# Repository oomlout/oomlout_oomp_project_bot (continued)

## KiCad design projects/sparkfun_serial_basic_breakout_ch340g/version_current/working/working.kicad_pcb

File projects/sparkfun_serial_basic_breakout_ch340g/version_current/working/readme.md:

# Serial_Basic_Breakout-CH340G by sparkfun  
This is a harvested standardized copy of a project from github.  
The original project can be found at:  
https://github.com/sparkfun/Serial_Basic_Breakout-CH340G  
Please consult that link for additional, details, files, and license information.  
Note: It was auto harvested and if the original repo had more than one board file or anything out of the ordinary the files here are likely not representative.

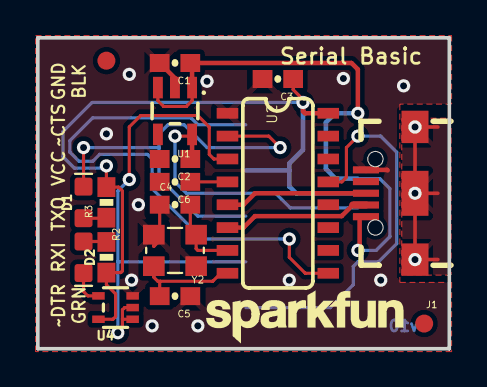
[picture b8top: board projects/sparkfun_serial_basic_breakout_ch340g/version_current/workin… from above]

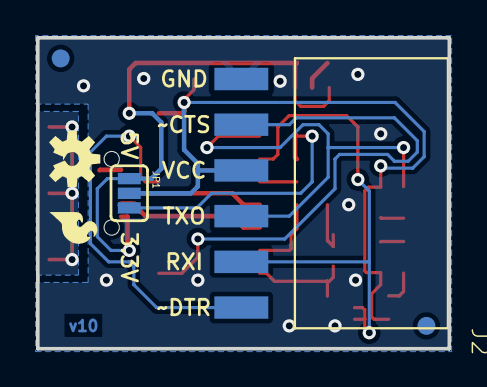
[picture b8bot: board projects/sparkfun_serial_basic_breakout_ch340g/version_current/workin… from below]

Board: 2 copper layers, 22.9 x 17.3 mm, 25 parts (6 on the bottom side), 17 nets.

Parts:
C1, C2: 1.0uF; 0603-CAP
C3: 0.1uF; 0603-CAP
C4, C5: 10pF; 0603-CAP
C6: 10nF; 0603-CAP
D1: GREEN; LED-0603
D2: Yellow; LED-0603
FRAME1: FRAME-LETTER; CREATIVE_COMMONS
J1: microB; USB-B-MICRO-SMD_V03
J2: 1X06-SMD-FEMALE-V2
JP1: PAD-JUMPER-3-2OF3_NC_BY_PASTE_YES_SILK_FULL_BOX
JP3, JP4, JP5, JP6: FIDUCIAL1X2; FIDUCIAL-1X2
LOGO1: OSHW-LOGOS; OSHW-LOGO-S
LOGO2: SFE_LOGO_FLAME.1_INCH; SFE_LOGO_FLAME_.1
LOGO3: SFE_LOGO_NAME.1_INCH; SFE_LOGO_NAME_.1
R2: 1K; 0603-RES
R3: 330; 0603-RES
U1: AP2112-3.3V; SOT23-5
U2: CH340G; SO016
U4: 74LVC1G08SE; SOT353
Y2: 12MHz; CRYSTAL-SMD-3.2X2.5

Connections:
3.3V: C2.1, JP1.3, U1.5
5V: C1.1, J1.VBUS, JP1.1, U1.1, U1.3
GND: C1.2, C2.2, C3.2, C4.1, C5.1, C6.2, J1.GND, J2.1, U1.2, U2.1, U4.3, Y2.2, Y2.4
unnamed: D1.A, R3.1
unnamed: D2.A, R2.1
unnamed: C5.2, U2.8, Y2.3
unnamed: C4.2, U2.7, Y2.1
unnamed: D2.C, U4.4
unnamed: J1.D-, U2.6
unnamed: J1.D+, U2.5
RXI: J2.5, U2.3, U4.1, U4.2
SHLD: J1.SHIELD1, J1.SHIELD2, J1.SHIELD3
TXO: D1.C, J2.4, U2.2
V3: C6.1, U2.4
VCC: C3.1, J2.3, JP1.2, R2.2, R3.2, U2.16, U4.5
~CTS: J2.2, U2.9
~DTR: J2.6, U2.13

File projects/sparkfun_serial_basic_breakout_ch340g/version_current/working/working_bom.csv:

"Id";"Designator";"Footprint";"Quantity";"Designation";"Supplier and ref";
1;"R3";"0603-RES";1;"330";;;
2;"JP4,JP3,JP5,JP6";"FIDUCIAL-1X2";4;"FIDUCIAL1X2";;;
3;"C1,C2";"0603-CAP";2;"1.0uF";;;
4;"C4,C5";"0603-CAP";2;"10pF";;;
5;"D2";"LED-0603";1;"Yellow";;;
6;"C6";"0603-CAP";1;"10nF";;;
7;"R2";"0603-RES";1;"1K";;;
8;"J1";"USB-B-MICRO-SMD_V03";1;"microB";;;
9;"U4";"SOT353";1;"74LVC1G08SE";;;
10;"FRAME1";"CREATIVE_COMMONS";1;"FRAME-LETTER";;;
11;"U1";"SOT23-5";1;"AP2112-3.3V";;;
12;"LOGO3";"SFE_LOGO_NAME_.1";1;"SFE_LOGO_NAME.1_INCH";;;
13;"Y2";"CRYSTAL-SMD-3.2X2.5";1;"12MHz";;;
14;"U2";"SO016";1;"CH340G";;;
15;"D1";"LED-0603";1;"GREEN";;;
16;"C3";"0603-CAP";1;"0.1uF";;;
17;"LOGO1";"OSHW-LOGO-S";1;"OSHW-LOGOS";;;
18;"J2";"1X06-SMD-FEMALE-V2";1;"";;;
19;"LOGO2";"SFE_LOGO_FLAME_.1";1;"SFE_LOGO_FLAME.1_INCH";;;
20;"JP1";"PAD-JUMPER-3-2OF3_NC_BY_PASTE_YES_SILK_FULL_BOX";1;"";;;

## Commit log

2023-07-30 a few generations
2023-07-31 some generations
2023-08-01 converted omerk brd to kicad
2023-08-02 a few projects
2023-08-02 some documentation
2023-08-03 more kicad files
2023-08-03 added kibot files for projects
2023-08-03 removed oom_kicad dependancy
2023-08-03 added print statement
2023-08-03 added kicad_sch check to deal with old kicad format issues
2023-08-03 more verbose command line arg.
2023-08-03 even more verbose.
2023-08-03 added an overwrite check
2023-08-03 first gitbot try
2023-08-03 up to date
2023-08-03 added some gitbot
2023-08-03 comitting after 1 generations
2023-08-03 comitting after 2 generations
2023-08-03 comitting after 30 generations
2023-08-03 comitting after 60 generations
2023-08-03 comitting after 90 generations
2023-08-03 comitting after 120 generations
2023-08-03 comitting after 150 generations
2023-08-03 comitting after 180 generations
2023-08-03 comitting after 210 generations
2023-08-03 comitting after 240 generations
2023-08-03 comitting after 270 generations
2023-08-03 comitting after 50 generations
2023-08-03 comitting after 100 generations
2023-08-03 comitting after 200 generations
2023-08-04 comitting after 250 generations
2023-08-04 comitting after 300 generations
2023-08-04 comitting after 350 generations
2023-08-04 comitting after 400 generations
2023-08-04 comitting after 450 generations
2023-08-04 comitting after 500 generations
2023-08-04 comitting after 550 generations
2023-08-04 comitting after 600 generations
2023-08-04 comitting after 650 generations
2023-08-04 a checkup
2023-08-04 more project translations
2023-08-04 adding some more renders
2023-08-05 comitting after 700 generations
2023-08-06 a few renders
2023-08-06 adding a few more eagle projects as kicad
2023-08-06 some stuff
2023-08-07 adding 775
2023-08-07 quick commit
2023-08-07 updated all projects from src
2023-08-07 a few extra
2023-08-07 a few gens
2023-08-07 oshcamp update
2023-08-07 oshcamp kicad_pcbs
2023-08-07 oshcamp gen
2023-08-07 added oshcamp bom
2023-08-08 bringing up to date.
2023-08-08 added readmes
2023-08-08 added oomp_key to project
2023-08-14 added parts_verbose
2023-08-16 added some converted schematics
2023-08-16 some schematic pdfs
2023-08-16 added a few rescued schematics
2023-08-17 more kicad older version rescues
2023-08-18 added some captures
2023-08-20 almost all rescued kicad schematics
2023-08-20 a bunch of harvesting
2023-08-27 some gens
2023-08-29 resyncing
2023-08-29 comitting after 5000 generations
2023-08-29 comitting after 10000 generations
2023-08-29 comitting after 15000 generations
2023-08-29 image resolutions
2023-08-30 added match md
2023-08-30 fixed projects.yaml location
2023-08-30 fixed link
2023-09-05 complete run
